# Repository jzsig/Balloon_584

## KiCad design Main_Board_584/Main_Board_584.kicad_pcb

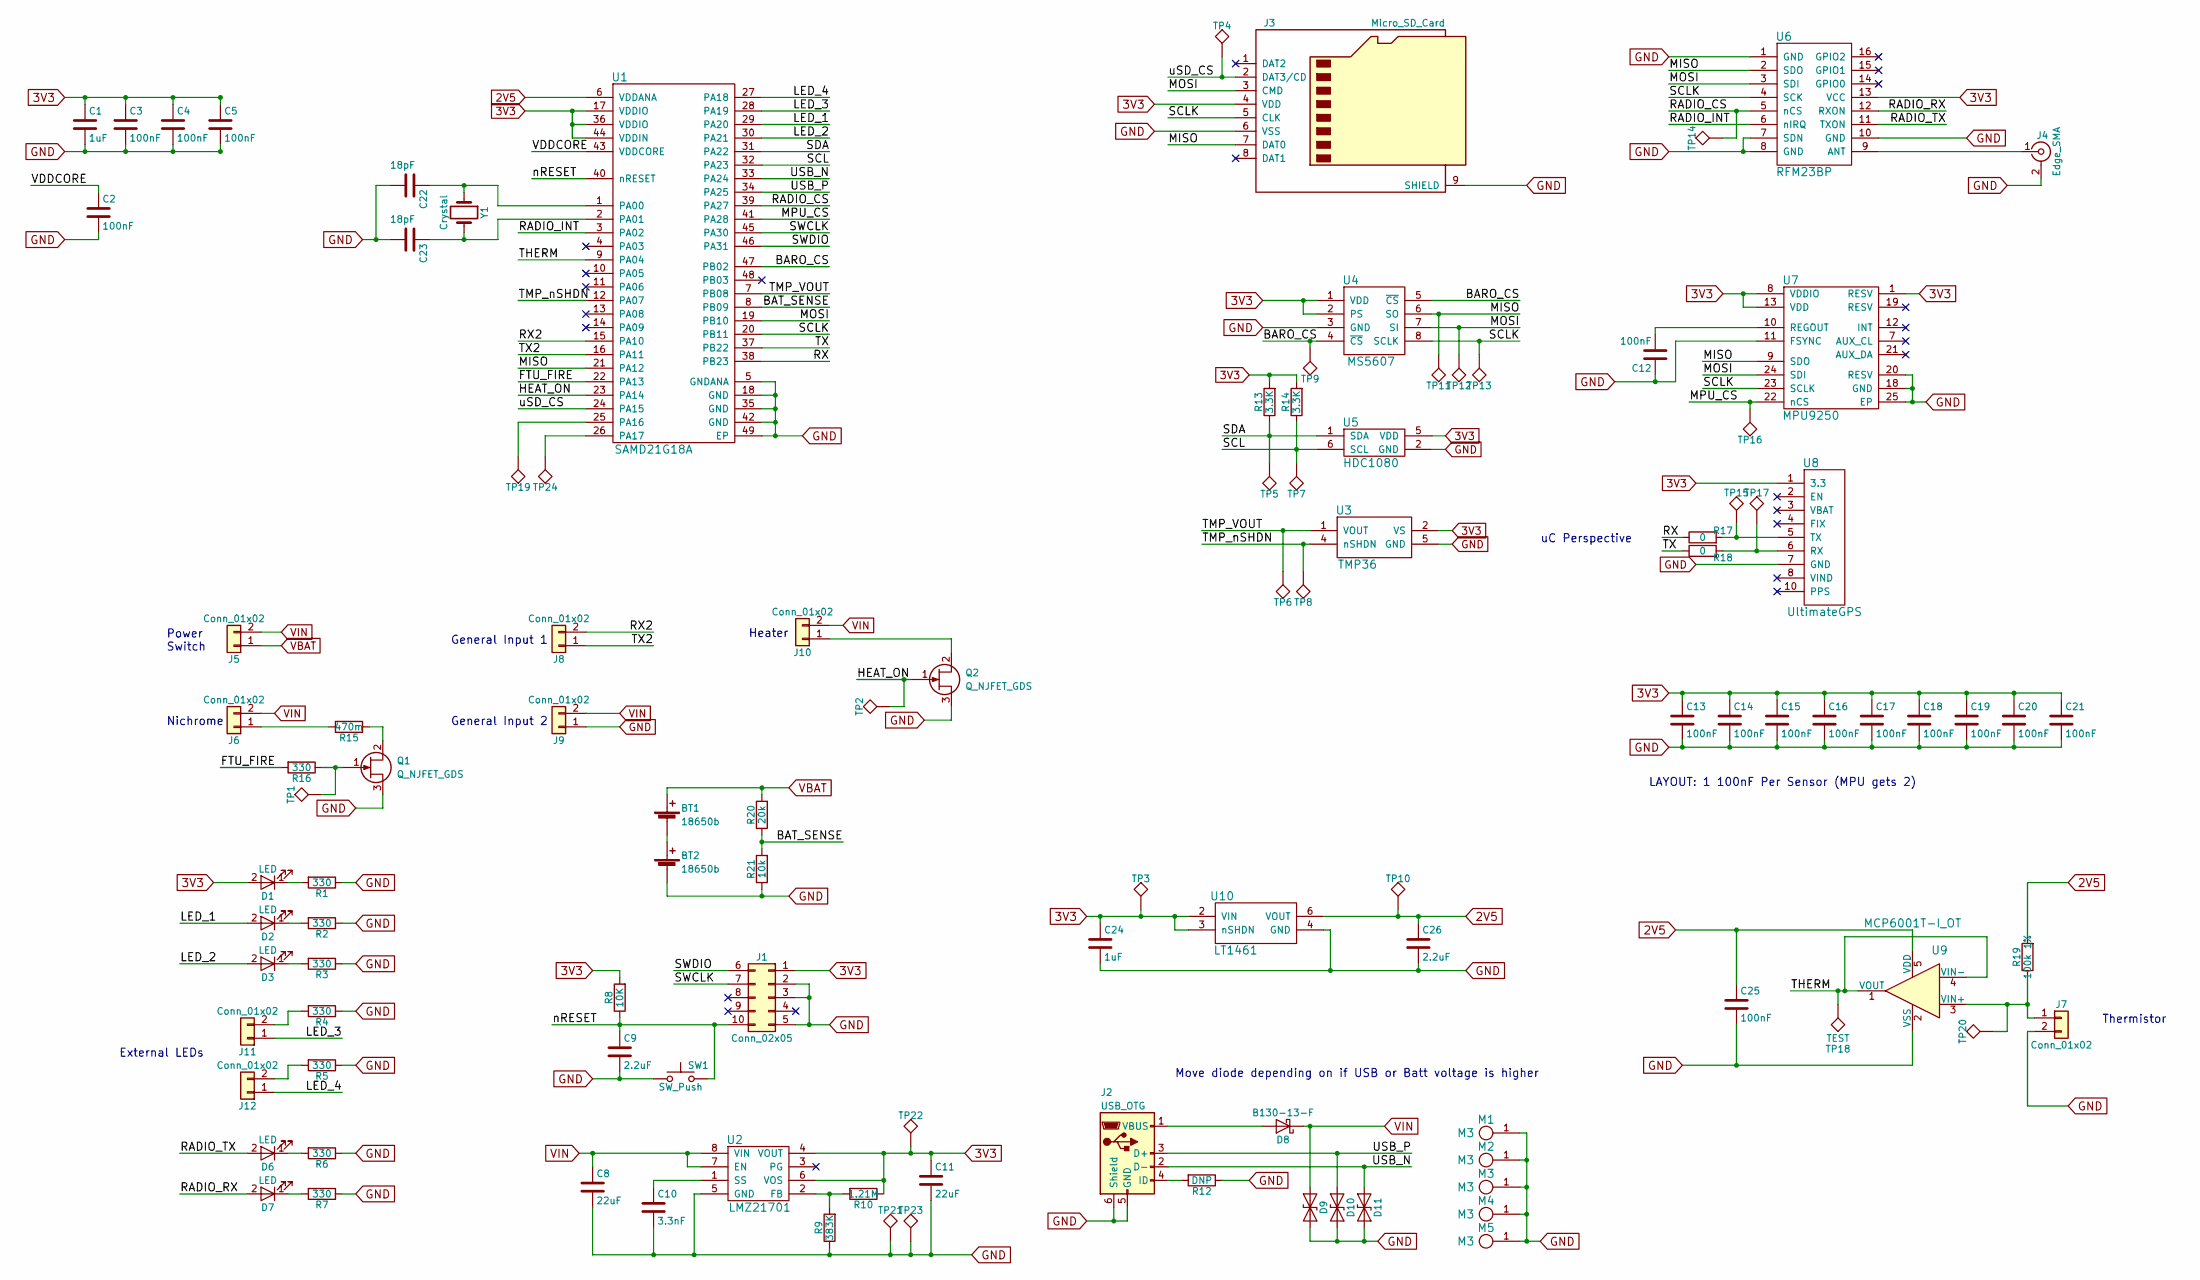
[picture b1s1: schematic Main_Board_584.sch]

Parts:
BT1, BT2: 18650b; 18650Holder
C1, C24: 1uF; C_0603
C2, C3, C4, C5, C12, C13, C14, C15, C16, C17, C18, C19, C20, C21, C25: 100nF; C_0603
C8, C11: 22uF; C_1206
C9, C26: 2.2uF; C_0603
C10: 3.3nF; C_0603
C22, C23: 18pF; C_0603
D1, D2, D3, D6, D7: LED; LED_0603
D8: B130-13-F; D_SMA
D9, D10, D11: CPDUR5V0HE-HF; D_0603
J1: Conn_02x05; M50-3600542
J2: USB_OTG; USB_Micro-B
J3: Micro_SD_Card; microSD_Card_Receptacle_Wuerth_693072010801
J4: Edge_SMA; EBAY_SMA
J5, J6, J7, J8, J9, J10, J11, J12: Conn_01x02; A33199CT-ND
M1, M2, M3, M4, M5: M3; M3Mounting_Hole
Q1, Q2: Q_NJFET_GDS; TO-220-3_Vertical
R1, R2, R3, R4, R5, R6, R7, R16: 330; C_0603
R8: 10K; C_0603
R9: 383K; C_0603
R10: 1.21M; C_0603
R12: DNP; C_0603
R13, R14: 3.3K; C_0603
R15: 470m; R_Axial_DIN0918_L18.0mm_D9.0mm_P25.40mm_Horizontal
R17, R18: 0; C_0603
R19: 100k 1%; C_0603
R20: 20k; C_0603
R21: 10k; C_0603
SW1: SW_Push; SW_SPST_B3U-1100P
TP1, TP2, TP3, TP4, TP5, TP6, TP7, TP8, TP9, TP10, TP11, TP12, TP13, TP14, TP15, TP16, TP17, TP18, TP19, TP20, TP21, TP22, TP23, TP24: TEST; 0603_TP
U1: SAMD21G18A; QFN-48-1EP_7x7mm_Pitch0.5mm
U2: LMZ21701
U3: TMP36; TSOT-23-5
U4: MS5607
U5: HDC1080; WSON-6
U6: RFM23BP
U7: MPU9250; QFN-24-1EP_3x3mm_Pitch0.4mm
U8: UltimateGPS
U9: MCP6001T-I_OT; SOT-23-5; MPN MCP6001T-I/OT; Digi-Key_PN MCP6001T-I/OTCT-ND
U10: LT1461; SOIC-8_3.9x4.9mm_Pitch1.27mm
Y1: Crystal; Crystal_SMD_EuroQuartz_EQ161-2pin_3.2x1.5mm

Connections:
2V5: C25.1, C26.1, R19.2, TP10.1, U1.6 (VDDANA), U9.5 (VDD), U10.6 (VOUT)
3V3: C1.1, C3.1, C4.1, C5.1, C11.1, C13.1, C14.1, C15.1, C16.1, C17.1, C18.1, C19.1, C20.1, C21.1, C24.1, D1.2 (A), J1.1, J3.4 (VDD), R8.2, R10.1, R13.2, R14.2, TP3.1, TP22.1, U1.17 (VDDIO), U1.36 (VDDIO), U1.44 (VDDIN), U2.4 (VOUT), U2.6 (VOS), U3.2 (VS), U4.1 (VDD), U4.2 (PS), U5.5 (VDD), U6.13 (VCC), U7.1 (RESV), U7.8 (VDDIO), U7.13 (VDD), U8.1 (3.3), U10.2 (VIN), U10.3 (nSHDN)
/BARO_CS: TP9.1, U1.47 (PB02), U4.4 (~CS), U4.5 (~CS)
/BAT_SENSE: R20.1, R21.2, U1.8 (PB09)
/FTU_FIRE: R16.2, U1.22 (PA13)
/HEAT_ON: Q2.1 (G), TP2.1, U1.23 (PA14)
/LED_1: D2.2 (A), U1.29 (PA20)
/LED_2: D3.2 (A), U1.30 (PA21)
/LED_3: J11.1, U1.28 (PA19)
/LED_4: J12.1, U1.27 (PA18)
/MISO: J3.7 (DAT0), TP11.1, U1.21 (PA12), U4.6 (SO), U6.2 (SDO), U7.9 (SDO)
/MOSI: J3.3 (CMD), TP12.1, U1.19 (PB10), U4.7 (SI), U6.3 (SDI), U7.24 (SDI)
/MPU_CS: TP16.1, U1.41 (PA28), U7.22 (nCS)
/RADIO_CS: TP14.1, U1.39 (PA27), U6.5 (nCS)
/RADIO_INT: U1.3 (PA02), U6.6 (nIRQ)
/RADIO_RX: D7.2 (A), U6.12 (RXON)
/RADIO_TX: D6.2 (A), U6.11 (TXON)
/RX: R17.1, U1.38 (PB23)
/RX2: J8.2, U1.15 (PA10)
/SCL: R14.1, TP7.1, U1.32 (PA23), U5.6 (SCL)
/SCLK: J3.5 (CLK), TP13.1, U1.20 (PB11), U4.8 (SCLK), U6.4 (SCK), U7.23 (SCLK)
/SDA: R13.1, TP5.1, U1.31 (PA22), U5.1 (SDA)
/SWCLK: J1.7, U1.45 (PA30)
/SWDIO: J1.6, U1.46 (PA31)
/THERM: TP18.1, U1.9 (PA04), U9.1 (VOUT), U9.4 (VIN-)
/TMP_VOUT: TP6.1, U1.7 (PB08), U3.1 (VOUT)
/TMP_nSHDN: TP8.1, U1.12 (PA07), U3.4 (nSHDN)
/TX: R18.1, U1.37 (PB22)
/TX2: J8.1, U1.16 (PA11)
/USB_N: D11.1 (A1), J2.2 (D-), U1.33 (PA24)
/USB_P: D10.1 (A1), J2.3 (D+), U1.34 (PA25)
/VDDCORE: C2.1, U1.43 (VDDCORE)
/nRESET: C9.1, J1.10, R8.1, SW1.2, U1.40 (nRESET)
/uSD_CS: J3.2 (DAT3/CD), TP4.1, U1.24 (PA15)
GND: BT2.2 (-), C1.2, C2.2, C3.2, C4.2, C5.2, C8.2, C9.2, C10.2, C11.2, C12.1, C13.2, C14.2, C15.2, C16.2, C17.2, C18.2, C19.2, C20.2, C21.2, C22.2, C23.2, C24.2, C25.2, C26.2, D9.2 (A2), D10.2 (A2), D11.2 (A2), J1.2, J1.3, J1.5, J2.5 (GND), J2.6 (Shield), J3.6 (VSS), J3.9 (SHIELD), J4.2 (Ext), J7.2, J9.1, M1.1, M2.1, M3.1, M4.1, M5.1, Q1.3 (S), Q2.3 (S), R1.1, R2.1, R3.1, R4.1, R5.1, R6.1, R7.1, R9.1, R12.1, R21.1, SW1.1, TP21.1, TP23.1, U1.5 (GNDANA), U1.18 (GND), U1.35 (GND), U1.42 (GND), U1.49 (EP), U2.5 (GND), U3.5 (GND), U4.3 (GND), U5.2 (GND), U6.1 (GND), U6.7 (SDN), U6.8 (GND), U6.10 (GND), U7.11 (FSYNC), U7.18 (GND), U7.20 (RESV), U7.25 (EP), U8.7 (GND), U9.2 (VSS), U10.4 (GND)
unnamed: BT1.2 (-), BT2.1 (+)
unnamed: C10.1, U2.1 (SS)
unnamed: C12.2, U7.10 (REGOUT)
unnamed: C22.1, U1.1 (PA00), Y1.1
unnamed: C23.1, U1.2 (PA01), Y1.2
unnamed: D1.1 (K), R1.2
unnamed: D2.1 (K), R2.2
unnamed: D3.1 (K), R3.2
unnamed: D6.1 (K), R6.2
unnamed: D7.1 (K), R7.2
unnamed: D8.2 (A), J2.1 (VBUS)
unnamed: J2.4 (ID), R12.2
unnamed: J4.1 (In), U6.9 (ANT)
unnamed: J6.1, R15.2
unnamed: J7.1, R19.1, TP20.1, U9.3 (VIN+)
unnamed: J10.1, Q2.2 (D)
unnamed: J11.2, R4.2
unnamed: J12.2, R5.2
unnamed: Q1.1 (G), R16.1, TP1.1
unnamed: Q1.2 (D), R15.1
unnamed: R9.2, R10.2, U2.2 (FB)
unnamed: R17.2, TP15.1, U8.5 (TX)
unnamed: R18.2, TP17.1, U8.6 (RX)
unnamed: TP19.1, U1.25 (PA16)
unnamed: TP24.1, U1.26 (PA17)
VBAT: BT1.1 (+), J5.1, R20.2
VIN: C8.1, D8.1 (K), D9.1 (A1), J5.2, J6.2, J9.2, J10.2, U2.7 (EN), U2.8 (VIN)

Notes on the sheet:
Move diode depending on if USB or Batt voltage is higher
LAYOUT: 1 100nF Per Sensor (MPU gets 2)
uC Perspective
Power Switch
Nichrome
Thermistor
General Input 1
General Input 2
Heater
External LEDs

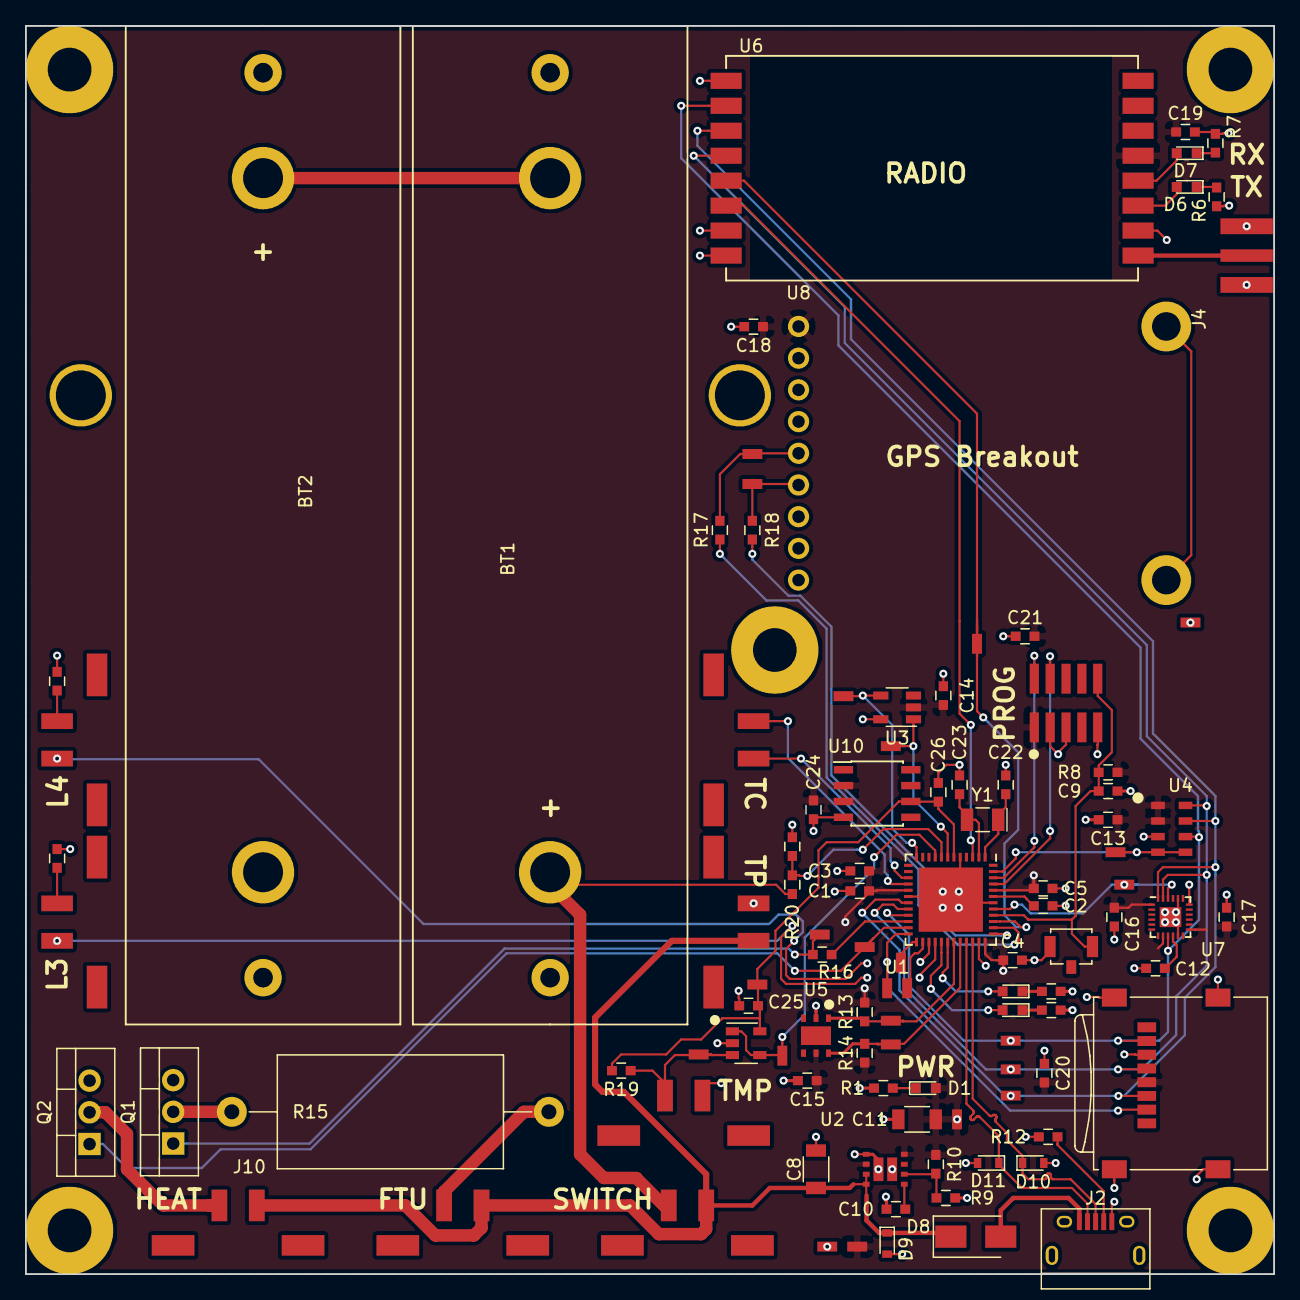
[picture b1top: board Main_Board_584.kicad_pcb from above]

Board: 4 copper layers, 100.0 x 100.0 mm, 110 parts (0 on the bottom side), 62 nets.

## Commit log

2018-01-13 :circus_tent: Added .gitattributes & .gitignore files
2018-01-13 Added Components
    Added Samd21
2018-01-13 SCH Improvementes
    Worked on sch
2018-01-16 Radio and uSD
    Finished radio and uSD
2018-01-28 Fixes
    Fixed some things
2018-01-28 Board Changes
2018-01-28 Added Kicad library
2018-01-29 added thermistor circuit
2018-01-29 Remembered to add chip identifier
2018-01-30 Added Reference
2018-01-30 Added Test Points
2018-01-30 Added Footprint Associations
2018-01-30 Mid Board Design
2018-01-30 Board Done
2018-02-02 Fixed Stuff
